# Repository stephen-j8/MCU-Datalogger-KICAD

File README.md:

# MCU-Datalogger-KICAD

## PROJECT OVERVIEW
MCU Datalogger — ATmega328P-based data logging PCB with DS1307 real-time clock, dual I²C EEPROM storage (24LC025 + 24LC1025), battery backup, UART/SPI/I²C breakout headers, and ICSP programming port. Designed in KiCad 10 on a 4-layer stackup. Includes full schematic, PCB layout, and Gerber files.

## CIRCUIT DETAILS
- ATmega328P-AU — 8-bit AVR MCU, 32KB Flash, 2KB SRAM, 1KB internal EEPROM
- DS1307 RTC — Real-time clock with battery backup (CR2032), accurate timekeeping even when power is off
- Dual I²C EEPROM — 24LC025 (2 Kbit) for config + 24LC1025 (1 Mbit / 128 KB) for data logging
- 16 MHz crystal — External clock for stable UART and precise timing
- 32.768 kHz crystal — Dedicated RTC oscillator (2¹⁵ Hz → 1 Hz via internal counter)
- Full I/O breakout — GPIO, UART, I²C, SPI headers for easy sensor/peripheral connection
- ICSP header — In-circuit programming without a bootloader
- 4-layer PCB — F.Cu / In1.Cu / In2.Cu / B.Cu stackup for clean power and signal integrity
- 4× mounting holes — M3, corner-placed for enclosure or standoff mounting

## TOOLS USED
  - SIMULATION-LTSpice
  - PCB(Schematic and layout capture)-KICAD
  - FABRICATION-JLCPCB

## FILES INCLUDED
  - GERBER FILES
  - LICENSE
  - PDF FILES
  - SCREENSHOTS
  - SOURCE FILES
  
## PCB PREVIEW

## SCHEMATIC PREVIEW

## BOM

## STATUS
 - Schematic Captured  
 - PCB Layout Captured
 - GERBERS Generated
   
## AUTHOR

STEPHEN.J - PCB DESIGN ENGINEER

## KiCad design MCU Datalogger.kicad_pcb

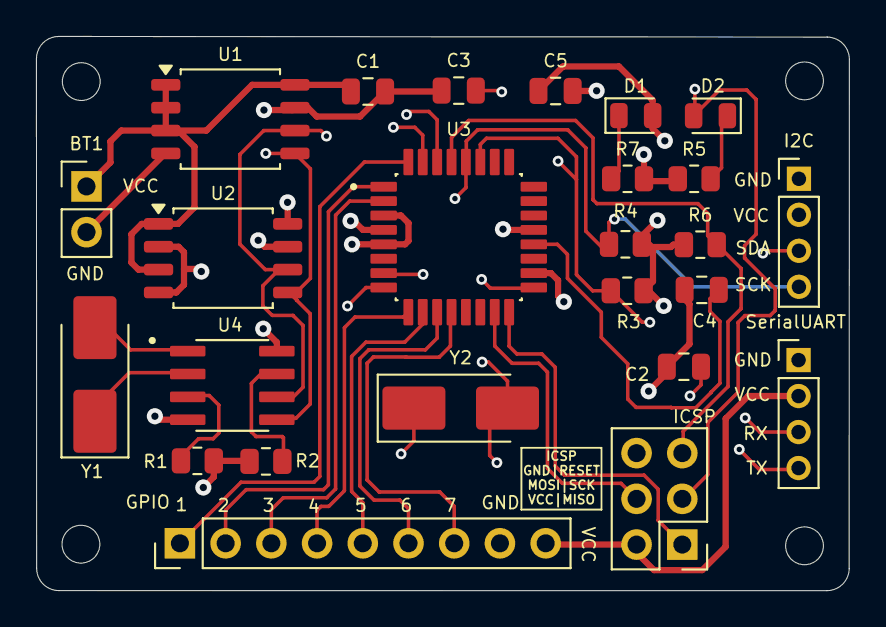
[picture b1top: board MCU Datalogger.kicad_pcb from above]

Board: 4 copper layers, 45.2 x 30.8 mm, 29 parts (0 on the bottom side), 26 nets.

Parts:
BT1: Battery; PinHeader_1x02_P2.54mm_Vertical
C1, C4: 0.1uF; C_0805_2012Metric
C2, C3: 22pF; C_0805_2012Metric
C5: 100nF; C_0805_2012Metric
D1, D2: LED; LED_0805_2012Metric
GPIO: Conn_01x09_Pin; PinHeader_1x09_P2.54mm_Vertical
H1, H2, H3, H4: MountingHole; MountingHole_2.1mm
I2C: Conn_01x04_Pin; PinHeader_1x04_P2.00mm_Vertical
ICSP: Conn_02x03_Odd_Even; PinHeader_2x03_P2.54mm_Vertical
R1, R2, R6: 10K; R_0805_2012Metric
R3, R4: 4.7K; R_0805_2012Metric
R5, R7: 330; R_0805_2012Metric
SerialUART: Conn_01x04_Pin; PinHeader_1x04_P2.00mm_Vertical
U1, U2: 24LC1025; SOIC-8_5.3x5.3mm_P1.27mm
U3: ATMEGA328P-AU; QFP80P900X900X120-32N
U4: DS1337S_; SOIC127P600X175-8N
Y1: 32.768 KHz; Crystal_SMD_5032-2Pin_5.0x3.2mm_HandSoldering
Y2: 16 MHz; Crystal_SMD_5032-2Pin_5.0x3.2mm_HandSoldering

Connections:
/D2: GPIO.1, U3.32 (PD2)
/D3: GPIO.2, U3.1 (PD3)
/D4: GPIO.3, U3.2 (PD4)
/D5: GPIO.4, U3.9 (PD5)
/D6: GPIO.5, U3.10 (PD6)
/D7: GPIO.6, U3.11 (PD7)
/D8: GPIO.7, U3.12 (PB0)
/MISO: ICSP.1, U3.16 (PB4)
/MOSI: ICSP.4, U3.15 (PB3)
/RESET: ICSP.5, R6.2, U3.29 (PC6/~RESET)
/RX: SerialUART.3, U3.30 (PD0)
/SCK: D2.2 (A), ICSP.3, U3.17 (PB5)
/SCL: I2C.4, R4.2, U1.6 (SCL), U2.6 (SCL), U3.28 (PC5), U4.6 (SCL)
/SDA: I2C.3, R3.2, U1.5 (SDA), U2.5 (SDA), U3.27 (PC4), U4.5 (SDA)
/TX: SerialUART.4, U3.31 (PD1)
/VCC: BT1.1 (+), C1.1, C5.1, D1.2 (A), GPIO.9, I2C.2, ICSP.2, R1.1, R2.1, R3.1, R4.1, R6.1, SerialUART.2, U1.1 (A0), U1.2 (A1), U1.3 (A2), U1.8 (VCC), U2.1 (A0), U2.3 (A2), U2.8 (VCC), U3.4 (VCC), U3.18 (AVCC), U4.8 (VCC)
GND: BT1.2 (-), C1.2, C2.1, C3.1, C4.1, C5.2, GPIO.8, I2C.1, ICSP.6, R5.1, R7.2, SerialUART.1, U1.4 (GND), U1.7 (WP), U2.2 (A1), U2.4 (GND), U2.7 (WP), U3.3 (GND), U3.5 (GND), U3.21 (GND), U4.4 (GND)
unnamed: D1.1 (K), R7.1
unnamed: D2.1 (K), R5.2
unnamed: C4.2, U3.20 (AREF)
unnamed: C2.2, U3.7 (PB6), Y2.2
unnamed: C3.2, U3.8 (PB7), Y2.1
unnamed: R2.2, U4.7 (SQW/~INT)
unnamed: U4.1 (X1), Y1.2
unnamed: U4.2 (X2), Y1.1
unnamed: R1.2, U4.3 (~INTA)

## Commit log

2026-06-04 GERBER-FILES
2026-06-04 SOURCE-FILES-KICAD
2026-06-04 SCREENSHOTS
2026-06-04 PDF-FILES
